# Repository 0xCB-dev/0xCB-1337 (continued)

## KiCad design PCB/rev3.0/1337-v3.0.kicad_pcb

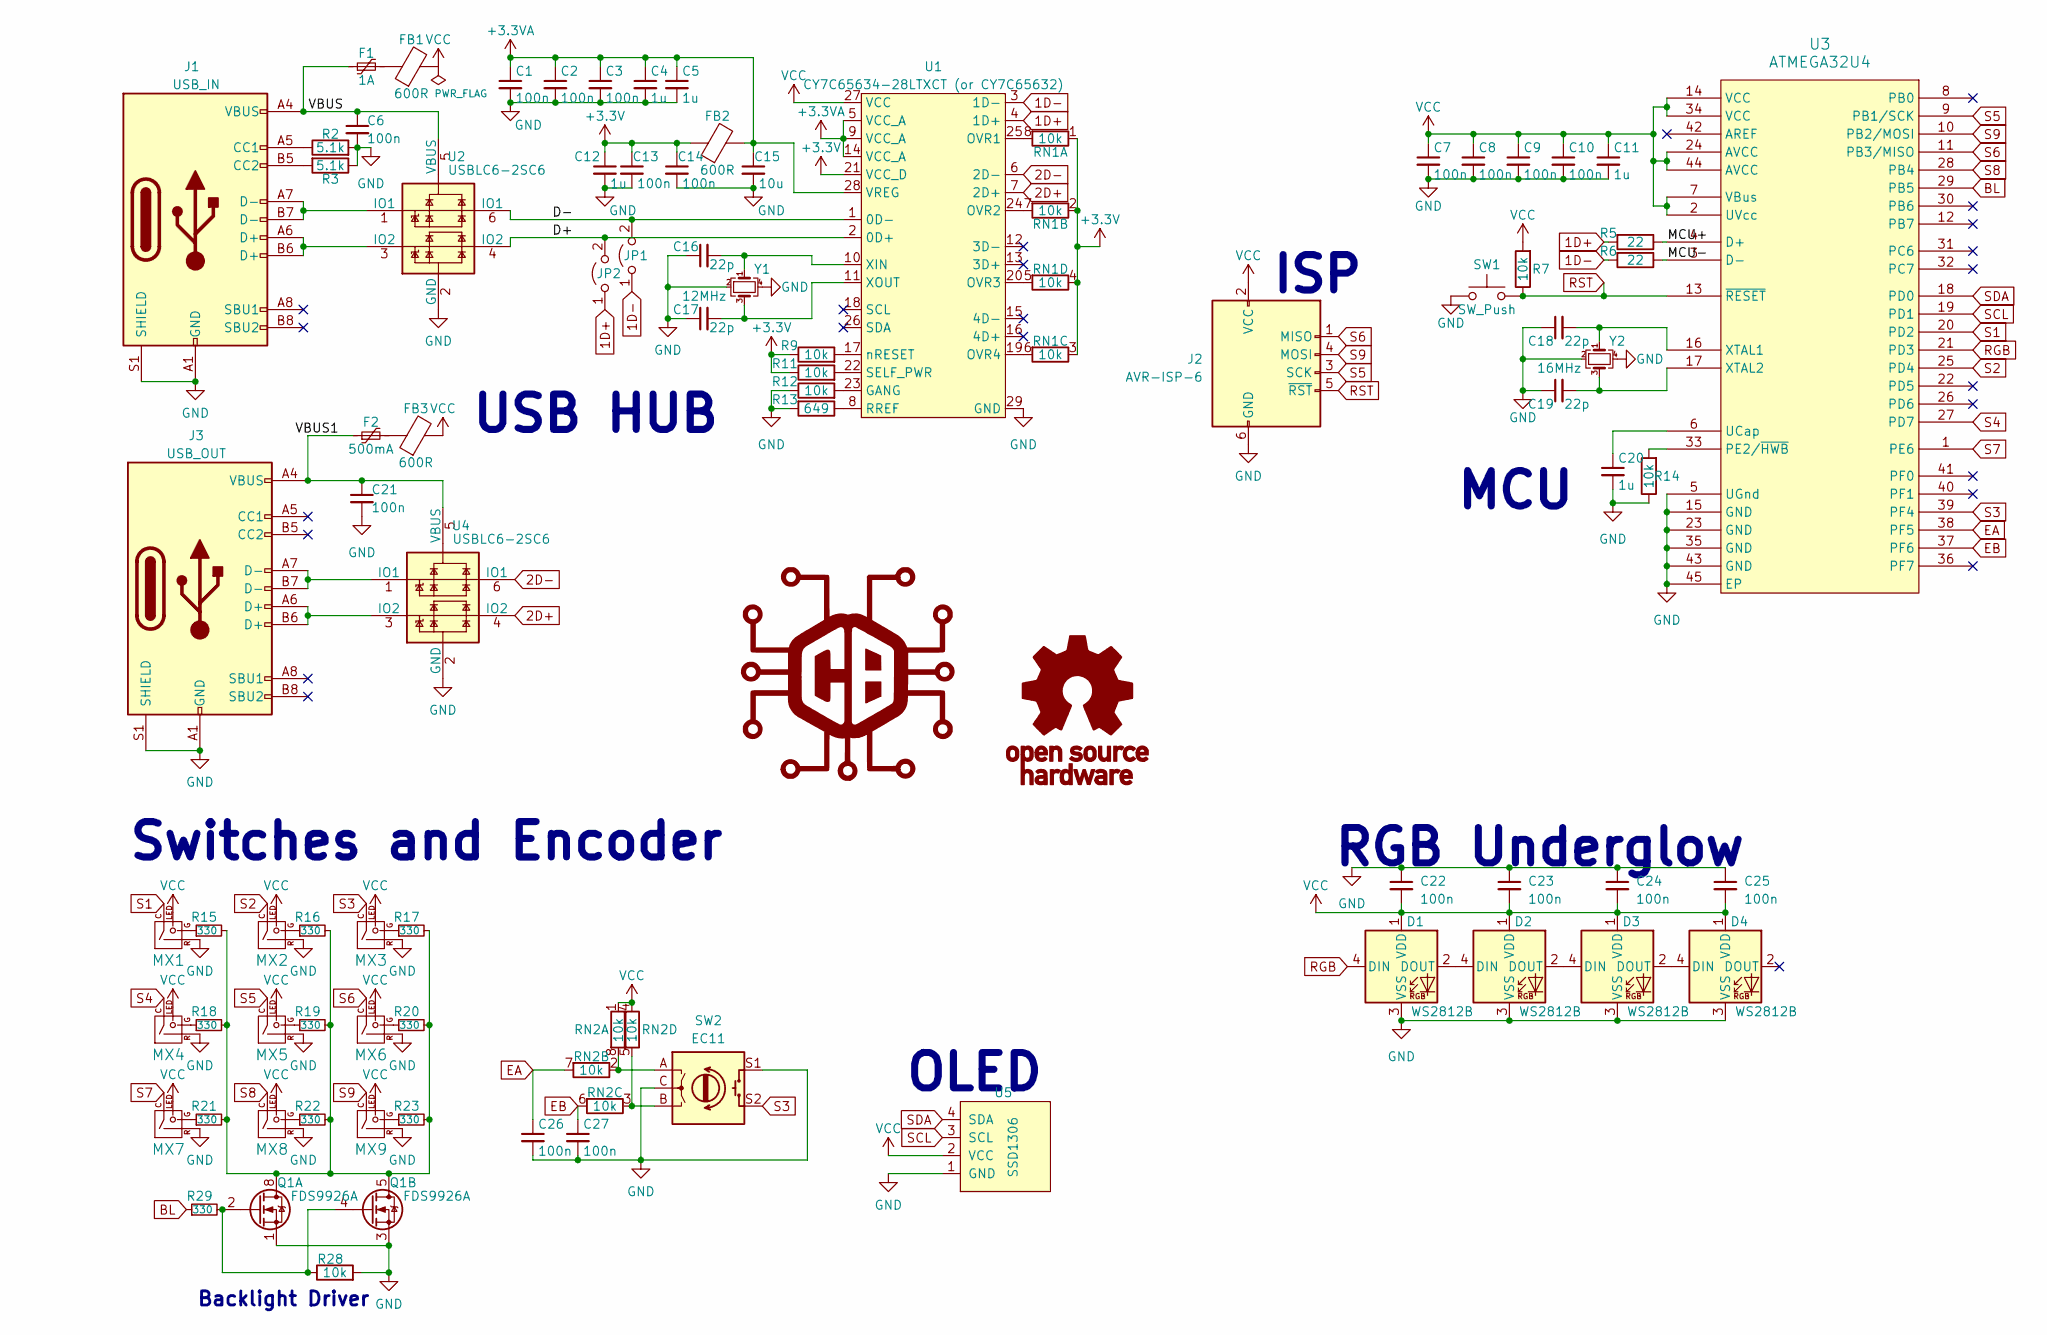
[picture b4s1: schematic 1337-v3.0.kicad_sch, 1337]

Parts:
C1, C2, C3, C6, C7, C8, C9, C10, C13, C14, C21, C22, C23, C24, C25, C26, C27: 100n; C_0603_1608Metric; Part Nb. 478-5266-1-ND
C4, C5, C11, C12, C20: 1u; C_0603_1608Metric; Part Nb. 1276-1102-1-ND
C15: 10u; C_0603_1608Metric; Part Nb. 587-3383-1-ND
C16, C17, C18, C19: 22p; C_0603_1608Metric; Part Nb. 478-1167-1-ND
D1, D2, D3, D4: WS2812B; LED_WS2812B_PLCC4_5.0x5.0mm_P3.2mm; Part Nb. 1568-COM-16347CT-ND
F1: 1A; Fuse_0805_2012Metric; Part Nb. 507-1815-1-ND
F2: 500mA; Fuse_0805_2012Metric; Part Nb. 507-1813-1-ND
FB1, FB2, FB3: 600R; Ferrite_Bead_0603; Part Nb. 732-1593-1-ND
J1: USB_IN; HRO-TYPE-C-31-M-13; Part Nb. 900-2169900002CT-ND
J2: AVR-ISP-6; AVR_PROG_2.54_THT
J3: USB_OUT; HRO-TYPE-C-31-M-13; Part Nb. 900-2169900002CT-ND
JP1, JP2: Jumper_2_Open; R_0201_0603Metric
L1: LOGO; logo
L2: OSHW; oshw
MX1, MX2, MX3, MX4, MX5, MX6, MX7, MX8, MX9: MX-LED; MXOnly-1U; Part Nb. CH310-ND
Q1: FDS9926A; SOIC-8_3.9x4.9mm_P1.27mm; Part Nb. FDS9926ACT-ND
R2, R3: 5.1k; R_0603_1608Metric; Part Nb. P5.1KDBCT-ND
R5, R6: 22; R_0603_1608Metric; Part Nb. A130081CT-ND
R7, R9, R11, R12, R14, R28: 10k; R_0603_1608Metric; Part Nb. RHM10KADCT-ND
R13: 649; R_0603_1608Metric; Part Nb. P649DBCT-ND
R15, R16, R17, R18, R19, R20, R21, R22, R23, R29: 330; R_1206_3216Metric; Part Nb. A130532CT-ND
RN1, RN2: 10k; R_Array_Convex_4x0603
SW1: SW_Push; SW_SPST_TL3342; Part Nb. EG2531CT-ND
SW2: EC11; RotaryEncoder_Alps_EC11E; Part Nb. PEC11L-4125F-S0020-ND
U1: CY7C65634-28LTXCT (or CY7C65632); QFN-28-1EP_5x5mm_P0.5mm_EP3.35x3.35mm_ThermalVias; Part Nb. 428-3154-1-ND
U2, U4: USBLC6-2SC6; SOT-23-6; Part Nb. 497-5235-1-ND
U3: ATMEGA32U4; QFN-44-1EP_7x7mm_P0.5mm_EP5.2x5.2mm_ThermalVias; Part Nb. ATMEGA32U4RC-MURCT-ND
U5: SSD1306; 128x64OLED
Y1: 12MHz; Crystal_SMD_3225-4Pin_3.2x2.5mm; Part Nb. XC2874CT-ND
Y2: 16MHz; Crystal_SMD_3225-4Pin_3.2x2.5mm; Part Nb. XC2060CT-ND

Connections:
1D+: JP2.1 (A), R5.2, U1.4 (1D+)
1D-: JP1.1 (A), R6.2, U1.3 (1D-)
2D+: U1.7 (2D+), U4.4 (IO2)
2D-: U1.6 (2D-), U4.6 (IO1)
+3.3VA: C1.1, C2.1, C3.1, C4.1, C5.1, C15.1, FB2.2, U1.5 (VCC_A), U1.9 (VCC_A), U1.14 (VCC_A), U1.28 (VREG)
+3V3: C12.1, C13.1, C14.1, FB2.1, R9.1, R11.1, RN1.1 (R1.1), RN1.2 (R2.1), RN1.3 (R3.1), RN1.4 (R4.1), U1.21 (VCC_D)
/D+: JP2.2 (B), U1.2 (0D+), U2.4 (IO2)
/D-: JP1.2 (B), U1.1 (0D-), U2.6 (IO1)
/MCU+: R5.1, U3.4 (D+)
/MCU-: R6.1, U3.3 (D-)
/VBUS: C6.1, F1.1, J1.A4 (VBUS), J1.A9 (VBUS), J1.B4 (VBUS), J1.B9 (VBUS), U2.5 (VBUS)
/VBUS1: C21.1, F2.1, J3.A4 (VBUS), J3.A9 (VBUS), J3.B4 (VBUS), J3.B9 (VBUS), U4.5 (VBUS)
BL: R29.1, U3.29 (PB5)
EA: C26.1, RN2.7 (R2.2), U3.38 (PF5)
EB: C27.1, RN2.6 (R3.2), U3.37 (PF6)
GND: C1.2, C2.2, C3.2, C4.2, C5.2, C6.2, C7.2, C8.2, C9.2, C10.2, C11.2, C12.2, C13.2, C14.2, C15.2, C16.1, C17.1, C18.1, C19.1, C20.2, C21.2, C22.1, C23.1, C24.1, C25.1, C26.2, C27.2, D1.3 (VSS), D2.3 (VSS), D3.3 (VSS), D4.3 (VSS), J1.A1 (GND), J1.A12 (GND), J1.B1 (GND), J1.B12 (GND), J1.S1 (SHIELD), J2.6 (GND), J3.A1 (GND), J3.A12 (GND), J3.B1 (GND), J3.B12 (GND), J3.S1 (SHIELD), MX1.2 (ROW), MX2.2 (ROW), MX3.2 (ROW), MX4.2 (ROW), MX5.2 (ROW), MX6.2 (ROW), MX7.2 (ROW), MX8.2 (ROW), MX9.2 (ROW), Q1.1 (S1), Q1.3 (S2), R2.2, R3.1, R12.1, R13.2, R14.1, R28.2, SW1.1, SW2.C, SW2.S1, U1.29 (GND), U2.2 (GND), U3.5 (UGnd), U3.15 (GND), U3.23 (GND), U3.35 (GND), U3.43 (GND), U3.45 (EP), U4.2 (GND), U5.1 (GND), Y1.2, Y1.4, Y2.2, Y2.4
unnamed: C16.2, U1.10 (XIN), Y1.1
unnamed: C17.2, U1.11 (XOUT), Y1.3
unnamed: C18.2, U3.16 (XTAL1), Y2.1
unnamed: C19.2, U3.17 (XTAL2), Y2.3
unnamed: C20.1, U3.6 (UCap)
unnamed: D1.2 (DOUT), D2.4 (DIN)
unnamed: D2.2 (DOUT), D3.4 (DIN)
unnamed: D3.2 (DOUT), D4.4 (DIN)
unnamed: F1.2, FB1.1
unnamed: F2.2, FB3.1
unnamed: J1.A5 (CC1), R2.1
unnamed: J1.A6 (D+), J1.B6 (D+), U2.3 (IO2)
unnamed: J1.A7 (D-), J1.B7 (D-), U2.1 (IO1)
unnamed: J1.B5 (CC2), R3.2
unnamed: J3.A6 (D+), J3.B6 (D+), U4.3 (IO2)
unnamed: J3.A7 (D-), J3.B7 (D-), U4.1 (IO1)
unnamed: MX1.4 (LEDGND), R15.1
unnamed: MX2.4 (LEDGND), R16.1
unnamed: MX3.4 (LEDGND), R17.1
unnamed: MX4.4 (LEDGND), R18.1
unnamed: MX5.4 (LEDGND), R19.1
unnamed: MX6.4 (LEDGND), R20.1
unnamed: MX7.4 (LEDGND), R21.1
unnamed: MX8.4 (LEDGND), R22.1
unnamed: MX9.4 (LEDGND), R23.1
unnamed: Q1.2 (G1), Q1.4 (G2), R28.1, R29.2
unnamed: Q1.5 (D2), Q1.6 (D2), Q1.7 (D1), Q1.8 (D1), R15.2, R16.2, R17.2, R18.2, R19.2, R20.2, R21.2, R22.2, R23.2
unnamed: R9.2, U1.17 (nRESET)
unnamed: R11.2, U1.22 (SELF_PWR)
unnamed: R12.2, U1.23 (GANG)
unnamed: R13.1, U1.8 (RREF)
unnamed: R14.2, U3.33 (PE2/~HWB)
unnamed: RN1.5 (R4.2), U1.20 (OVR3)
unnamed: RN1.6 (R3.2), U1.19 (OVR4)
unnamed: RN1.7 (R2.2), U1.24 (OVR2)
unnamed: RN1.8 (R1.2), U1.25 (OVR1)
unnamed: RN2.2 (R2.1), RN2.8 (R1.2), SW2.A
unnamed: RN2.3 (R3.1), RN2.5 (R4.2), SW2.B
RGB: D1.4 (DIN), U3.21 (PD3)
RST: J2.5 (~RST), R7.1, SW1.2, U3.13 (~RESET)
S1: MX1.1 (COL), U3.20 (PD2)
S2: MX2.1 (COL), U3.25 (PD4)
S3: MX3.1 (COL), SW2.S2, U3.39 (PF4)
S4: MX4.1 (COL), U3.27 (PD7)
S5: J2.3 (SCK), MX5.1 (COL), U3.9 (PB1/SCK)
S6: J2.1 (MISO), MX6.1 (COL), U3.11 (PB3/MISO)
S7: MX7.1 (COL), U3.1 (PE6)
S8: MX8.1 (COL), U3.28 (PB4)
S9: J2.4 (MOSI), MX9.1 (COL), U3.10 (PB2/MOSI)
SCL: U3.19 (PD1), U5.3 (SCL)
SDA: U3.18 (PD0), U5.4 (SDA)
VCC: C7.1, C8.1, C9.1, C10.1, C11.1, C22.2, C23.2, C24.2, C25.2, D1.1 (VDD), D2.1 (VDD), D3.1 (VDD), D4.1 (VDD), FB1.2, FB3.2, J2.2 (VCC), MX1.3 (LED), MX2.3 (LED), MX3.3 (LED), MX4.3 (LED), MX5.3 (LED), MX6.3 (LED), MX7.3 (LED), MX8.3 (LED), MX9.3 (LED), R7.2, RN2.1 (R1.1), RN2.4 (R4.1), U1.27 (VCC), U3.2 (UVcc), U3.7 (VBus), U3.14 (VCC), U3.24 (AVCC), U3.34 (VCC), U3.44 (AVCC), U5.2 (VCC)

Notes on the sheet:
Backlight Driver
USB HUB
Switches and Encoder
OLED
ISP
MCU
RGB Underglow

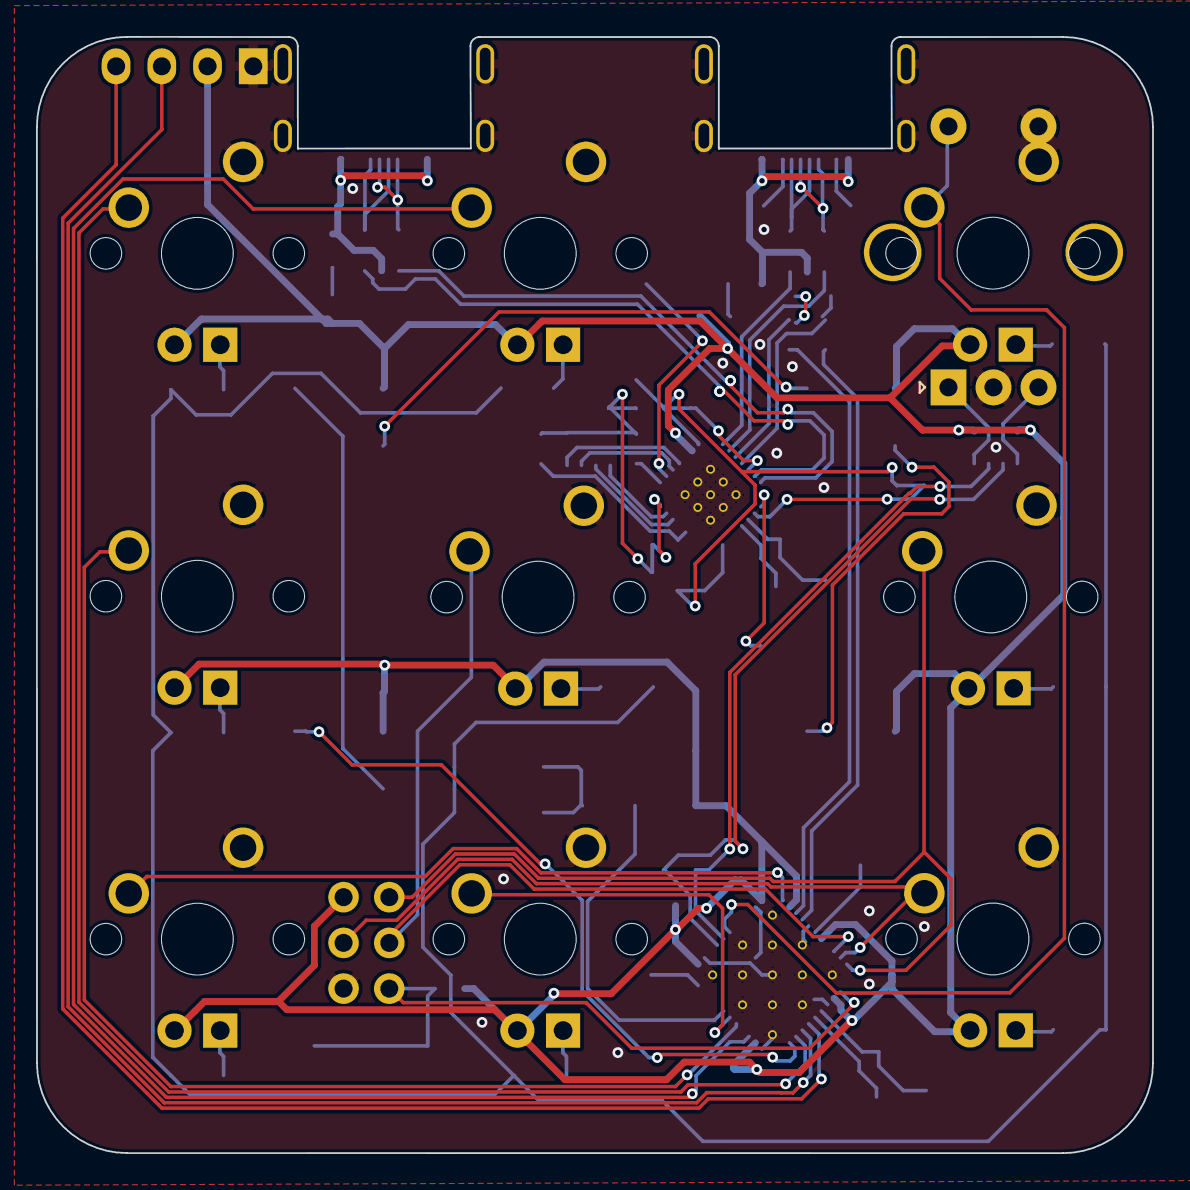
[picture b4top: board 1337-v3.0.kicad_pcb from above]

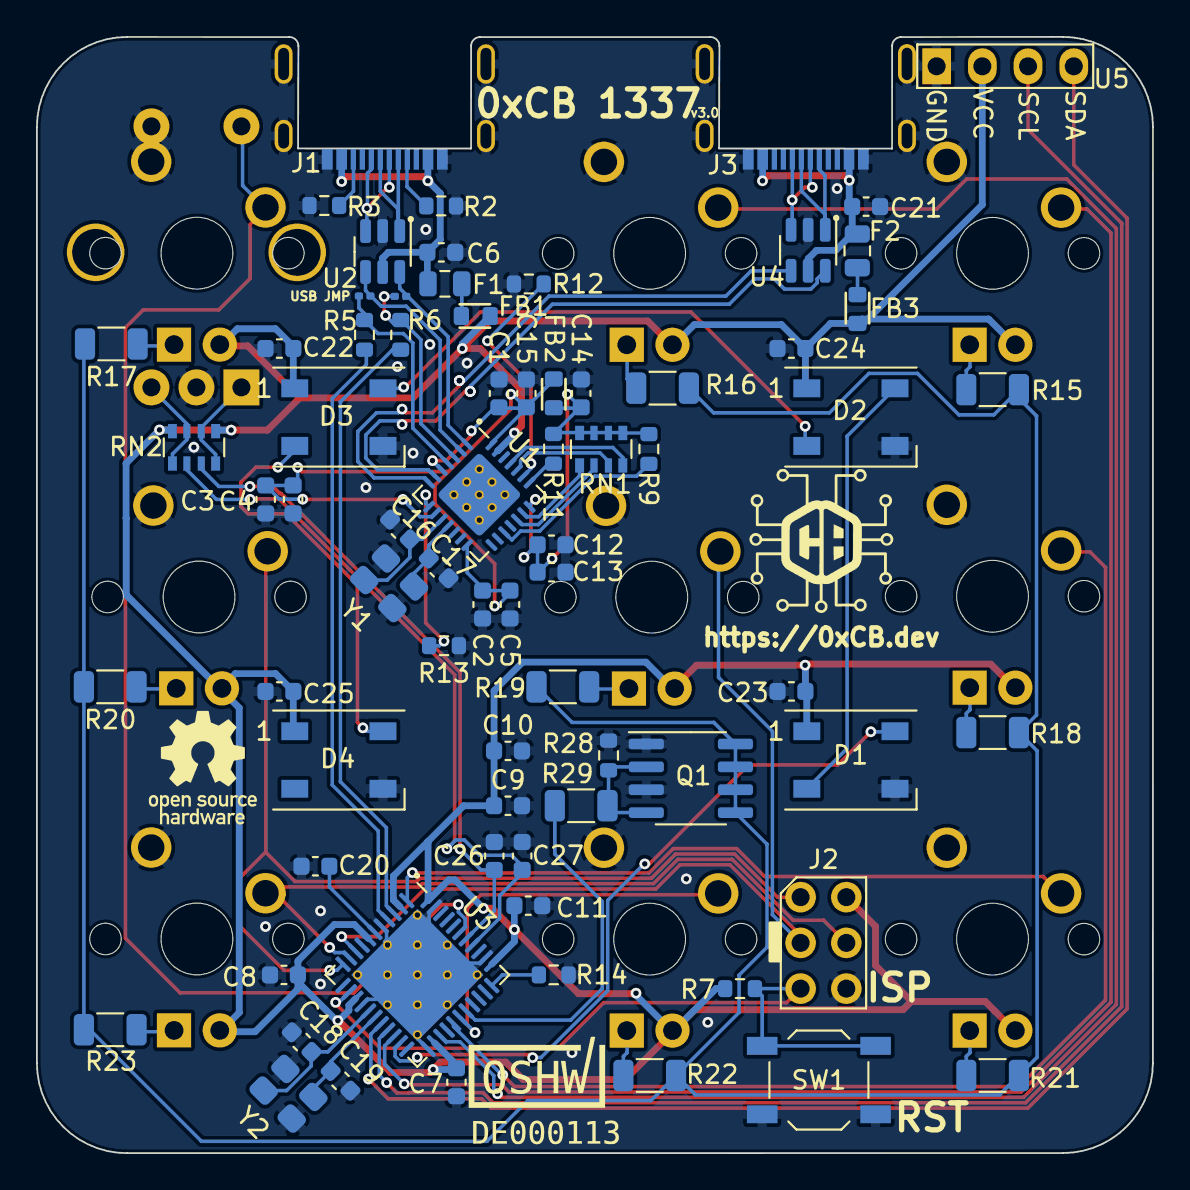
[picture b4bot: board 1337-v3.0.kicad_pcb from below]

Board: 2 copper layers, 62.0 x 62.0 mm, 86 parts (76 on the bottom side), 68 nets.

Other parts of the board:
L***: oshwa

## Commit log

2021-02-22 Add Files
2021-02-23 Added via.json
2021-02-23 Added Licence headers
2021-03-02 added licence and updated revision for better traces and smd componets + ISP flash header for easier flashing
2021-03-02 svg to file for md
2021-03-03 Folder to submodules
2021-03-03 try again
2021-03-03 now???
2021-03-03 FKN finally
2021-03-03 Tha branch :_:
2021-03-05 Merged :O
2021-03-05 Added instructions
2021-03-06 Updated designators
2021-03-06 Add binary
2021-03-19 Added images
2021-03-21 rev1.1 breaking updates
2021-03-22 update submodule
2021-03-24 added image
2021-03-24 well
2021-03-24 removed bars from image
2021-03-24 removed hex
2021-03-24 added oshwa cert
2021-03-28 added tindie link
2021-03-28 added more images
2021-03-28 updated submodules
2021-04-08 updated keycap img
2021-04-09 updated submodules to new repo
2021-04-17 updated OSHWA
2021-04-17 updated svg
2021-04-25 update color img
2021-05-22 added rev2.0
2021-05-24 added rev2.1
2021-05-25 v3.0
2021-05-28 v3-proto
2021-05-28 update bom
2021-05-30 updated bom
2021-06-26 updated readme bom
2021-12-13 added V4 WIP
2021-12-15 traced PCB
2021-12-15 rounded traces, added logo etc
2021-12-15 prod push
2022-01-03 docs: fix incorrect links in README
2022-01-07 finalizing v4.0
2022-01-07 fixing Readme
2022-01-07 updated BOM for v4.0
2022-01-07 added teardrops
2022-01-07 added gitignore
2022-01-07 added case models
2022-01-07 fixed links in README
2022-01-08 added 3D PCB models
2022-01-09 added OSHWA mark and exported prod files
2022-01-18 updated ibom link
2022-08-24 updated git
2022-08-24 small readme adjustment
2022-08-24 git update
2023-04-26 rev5 init
2023-04-27 added flex cable
2023-04-27 prod file generation
2023-05-29 fix some minor issues
2023-06-28 fix flex and expose GPIOs
